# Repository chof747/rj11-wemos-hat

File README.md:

## rj11-wemos-hat
Stack-up board for the [wemos-mains-dev board](https://github.com/chof747/wemos-mains-dev) which includes 2 RJ11 connectors that can be connected via solder pads to the broken out pins of the wemos D1 mini on the main board.

The board has the form factor to be stacked up on the wemos mains dev board to enable mains powered wifi enabled 
microcontroller projects

### Elements

- 2 RJ11 Connectors
- Solder pads for all wemos pins (except 5V, 3V3 and GND)
- 2 1x2 connector pads exposing the data lines of the RJ11s
- 2 Jumpers to select the available 5V or 3V3 rail for the RJ11 connector
- A push button for the reset and a push button for the flash pin of the wemos D1 mini + pull-ups 
 
## Used Parts:

## Revision History:

- **v1.0**: Initial version (Produced: 19.08.2023; First Assembly: 06.10.2023)
- **v1.1**: Corrected RJ12 socket connector

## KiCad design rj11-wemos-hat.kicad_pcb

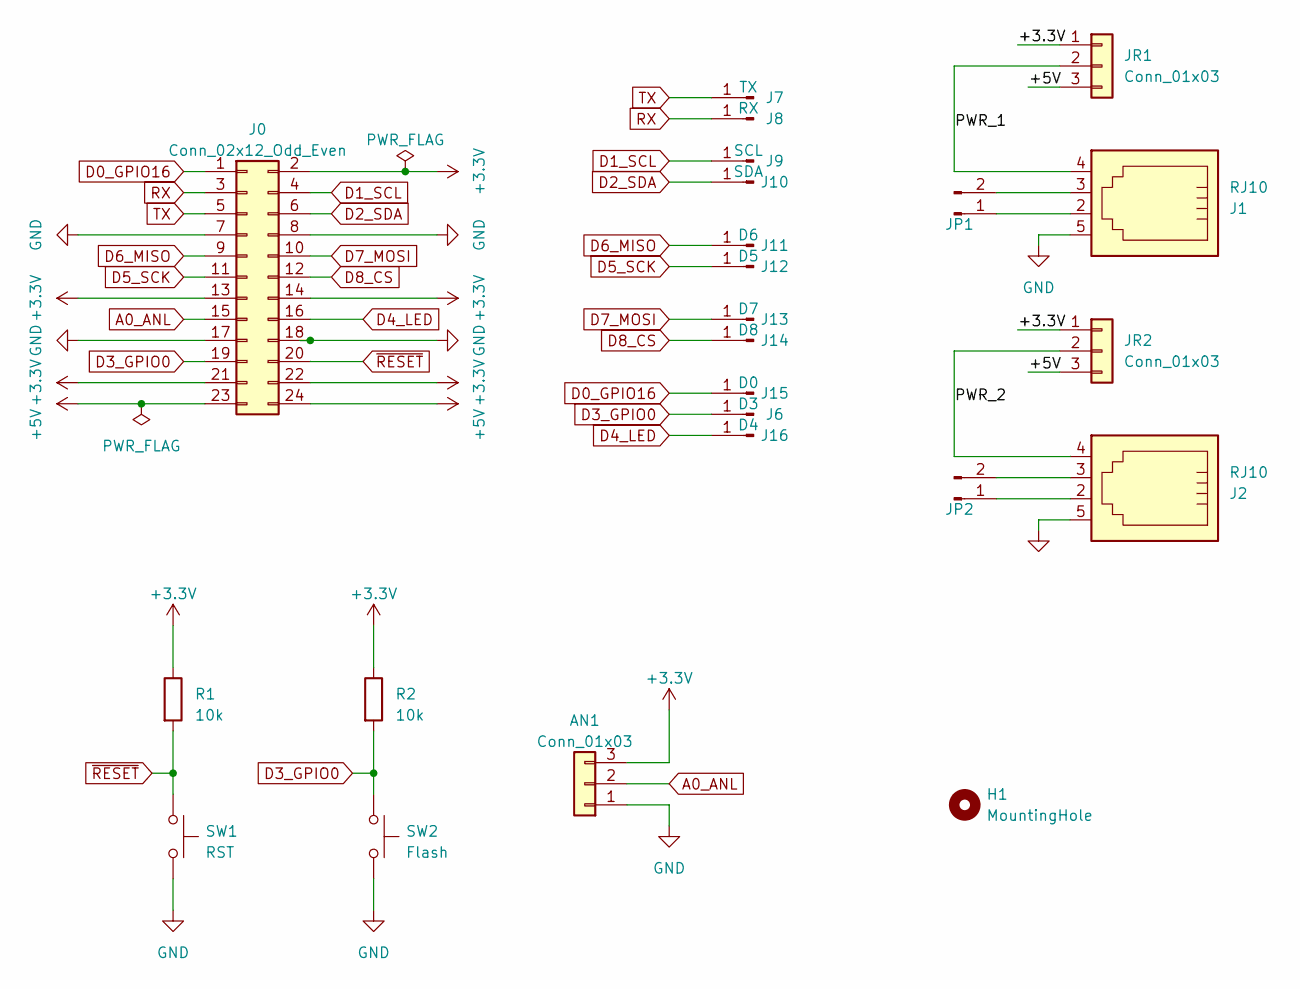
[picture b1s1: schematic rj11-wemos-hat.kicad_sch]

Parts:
AN1: Conn_01x03; PinHeader_1x03_P2.54mm_Vertical
H1: MountingHole; MountingHole_3mm
J0: Conn_02x12_Odd_Even; PinSocket_2x12_P2.54mm_Vertical
J1, J2: RJ10; RJ12_Amphenol_54601
J6: D3; Solder Pad 1x1 1.5x3
J7: TX; Solder Pad 1x1 1.5x3
J8: RX; Solder Pad 1x1 1.5x3
J9: SCL; Solder Pad 1x1 1.5x3
J10: SDA; Solder Pad 1x1 1.5x3
J11: D6; Solder Pad 1x1 1.5x3
J12: D5; Solder Pad 1x1 1.5x3
J13: D7; Solder Pad 1x1 1.5x3
J14: D8; Solder Pad 1x1 1.5x3
J15: D0; Solder Pad 1x1 1.5x3
J16: D4; Solder Pad 1x1 1.5x3
JP1, JP2: Solder Pad 1x2 1.5x3
JR1, JR2: Conn_01x03; PinHeader_1x03_P2.54mm_Vertical
R1, R2: 10k; R_0603_1608Metric_Pad0.98x0.95mm_HandSolder
SW1: RST; SW_PUSH_6mm
SW2: Flash; SW_PUSH_6mm

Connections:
+3.3V: AN1.3, J0.2, J0.13, J0.14, J0.21, J0.22, JR1.1, JR2.1, R1.1, R2.1; also elsewhere on the board
+5V: J0.23, J0.24, JR1.3, JR2.3; also elsewhere on the board
/PWR_1: J1.4, JR1.2
/PWR_2: J2.4, JR2.2; also elsewhere on the board
A0_ANL: AN1.2, J0.15
D0_GPIO16: J0.1, J15.1
D1_SCL: J0.4, J9.1
D2_SDA: J0.6, J10.1
D3_GPIO0: J0.19, J6.1, R2.2, SW2.1
D4_LED: J0.16, J16.1
D5_SCK: J0.11, J12.1
D6_MISO: J0.9, J11.1
D7_MOSI: J0.10, J13.1
D8_CS: J0.12, J14.1
GND: AN1.1, J0.7, J0.8, J0.17, J0.18, J1.5, J2.5, SW1.2, SW2.2
unnamed: J1.2, JP1.1
unnamed: J1.3, JP1.2
unnamed: J2.2, JP2.1
unnamed: J2.3, JP2.2
RX: J0.3, J8.1
TX: J0.5, J7.1
~RESET: J0.20, R1.2, SW1.1

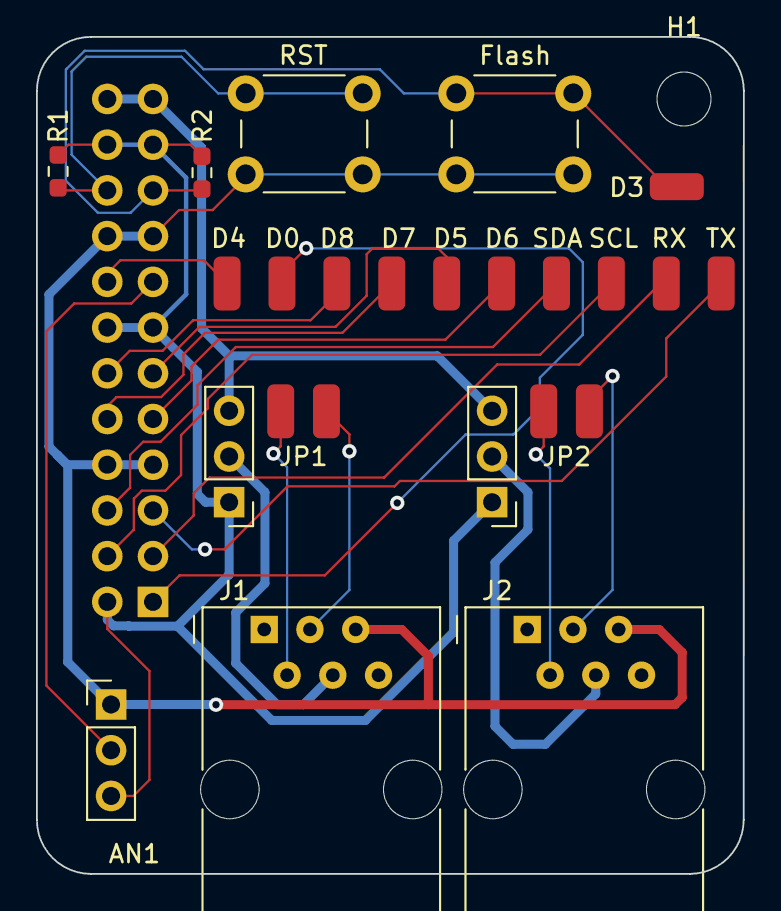
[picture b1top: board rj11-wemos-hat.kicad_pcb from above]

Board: 2 copper layers, 39.3 x 46.5 mm, 24 parts (1 on the bottom side), 22 nets.

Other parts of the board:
locked: Conn_01x03; PinHeader_1x03_P2.54mm_Vertical

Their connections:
+3.3V: locked.1; also elsewhere on the board
+5V: locked.3; also elsewhere on the board
/PWR_2: locked.2; also elsewhere on the board

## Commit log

2023-08-04 First complete Draft
2023-08-19 Initial version (Revision 1.0)
2023-09-15 corrected RJ12 socket Connector
2023-10-06 Format changes and first assembly
2024-02-10 added board outline
